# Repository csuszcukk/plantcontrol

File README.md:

# PlantControl
make a smart pot for plants

## Features

* Automatic watering and light control
* Humidity and temperature monitoring
* Soil temperature and moisture monitoring
* Low water level alert
* Custom water container design
* Compatible with all plants and pots

## How to Build It

1. **PCB Fabrication:** Order the PCBs from any manufacturer (ordering a stencil is recommended).
2. **Heat Dissipation (Optional):** If you plan to use LEDs, mount them on an aluminum sheet using thermal conductive tape for proper heat dissipation.
3. **Components:** Order the necessary components listed in the Bill of Materials (BOM) — feel free to modify or skip non-essential parts.
4. **3D Printing:** Print the structural parts (PLA is recommended for the main board enclosure, and PETG for the water container).
5. **Assembly:** Solder all components onto the PCB.
6. **Preparation:** Connect the boot configuration pins and plug in the power source.
7. **Flashing Interface:** Connect your USB-to-UART bridge (make sure RX and TX lines are swapped).
8. **Firmware Installation (MicroPython):** Flash the ESP32 with the MicroPython firmware (see the official [MicroPython ESP32 Documentation](https://docs.micropython.org/en/latest/esp32/tutorial/intro.html)).
9. **Uploading Code:** Flash `main.py` onto the board (follow this [MicroPython Flashing Guide](https://georgefreedom.com/ignition-sequence-how-to-flash-micropython-onto-your-esp32/)).
10. **Cleanup:** Remove the boot mode jumpers and the UART adapter, then disconnect power.
11. **Wiring:** Connect all peripherals and modules to their respective header pins (labels are silkscreened on the PCB for guidance).
12. **Final Mounting:** Secure the sensors and the main board inside the enclosure (double-sided mounting tape works great).
13. **Power On:** Reconnect power to the board.
14. **Done!** Your plant controller is ready to go.

> **Pro Tip:** On first boot (or if it cannot connect to a saved network), the device will host a Wi-Fi Access Point. Connect to it to enter your local Wi-Fi SSID and password via the captive portal. Don't forget to enter your ThingSpeak API key in the configuration file to enable telemetry logging!

## How It Works

PlantControl is an automated, ESP32-C6-powered plant monitoring and maintenance system running on custom MicroPython firmware. It continuously monitors environmental conditions and manages irrigation and lighting using asynchronous event loops.

### Core Architecture

* **Sensor Data Acquisition:** The system periodically samples soil moisture, ambient light, and air temperature/humidity levels. 
* **Automated Logic & Safety:** If soil moisture drops below the predefined threshold, the MCU triggers a relay/MOSFET to activate the water pump. It includes safety timers to prevent over-watering or running the pump dry.
* **Local UI & Status:** A circular GC9A01 SPI display provides real-time readout of plant metrics and device status directly on the enclosure.
* **Power & Load Management:** High-side MOSFET switching ensures power is delivered efficiently to peripherals (pumps, LEDs) only when needed, minimizing idle power consumption.
* **Connectivity & Telemetry:** Integrated Wi-Fi connects to local infrastructure to stream telemetry to ThingSpeak. If network connection fails, it automatically spins up a Wi-Fi Access Point with a captive portal for re-configuration.

## Component Sourcing & Logistics

To optimize the project budget and lead times, a hybrid sourcing strategy is used:

- **LCSC:** Used for standard SMD components, passives, ICs, and microcontrollers to take advantage of low bulk pricing.
- **HESTORE (EU Local Distributor):** Used for specific sensors, modules, and components unavailable on LCSC or needed quickly.

All BOM prices from HESTORE have been converted from HUF to USD using current market exchange rates.

## License

This project is licensed under the MIT License - see the [LICENSE](LICENSE) file for details.

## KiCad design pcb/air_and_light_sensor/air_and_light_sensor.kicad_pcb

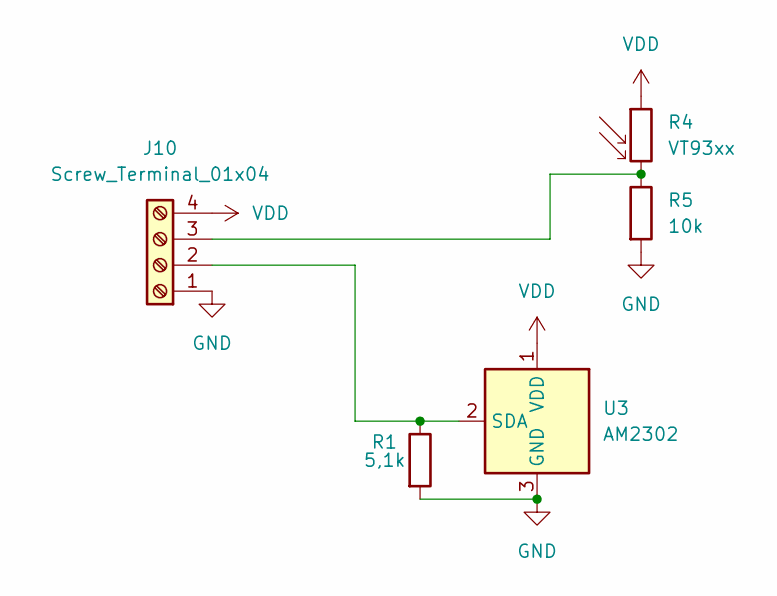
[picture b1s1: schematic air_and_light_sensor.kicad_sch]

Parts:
J10: Screw_Terminal_01x04; TerminalBlock_Phoenix_MKDS-1,5-4_1x04_P5.00mm_Horizontal; jlc part # C90087
R1: 5,1k; R_0603_1608Metric_Pad0.98x0.95mm_HandSolder
R4: VT93xx; R_LDR_4.9x4.2mm_P2.54mm_Vertical; jlc part # C10077
R5: 10k; R_0603_1608Metric_Pad0.98x0.95mm_HandSolder; jlc part # C2906982
U3: AM2302; ASAIR_AM2302_P2.54mm_Lead2.75mm_TabDown; jlc part # C83988

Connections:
GND: J10.1, R1.2, R5.2, U3.3 (GND), U3.4 (GND)
unnamed: J10.2, R1.1, U3.2 (SDA)
unnamed: J10.3, R4.2, R5.1
VDD: J10.4, R4.1, U3.1 (VDD)

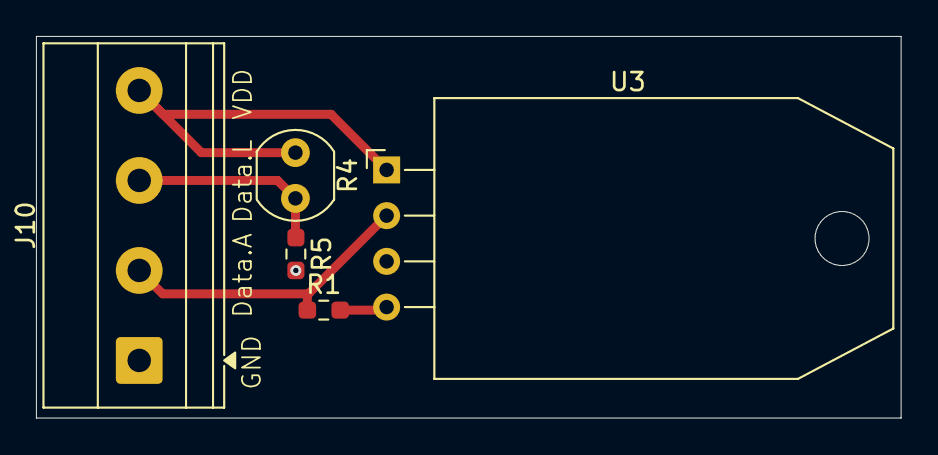
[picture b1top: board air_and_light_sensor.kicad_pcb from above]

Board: 2 copper layers, 48.0 x 21.2 mm, 5 parts (0 on the bottom side), 4 nets.

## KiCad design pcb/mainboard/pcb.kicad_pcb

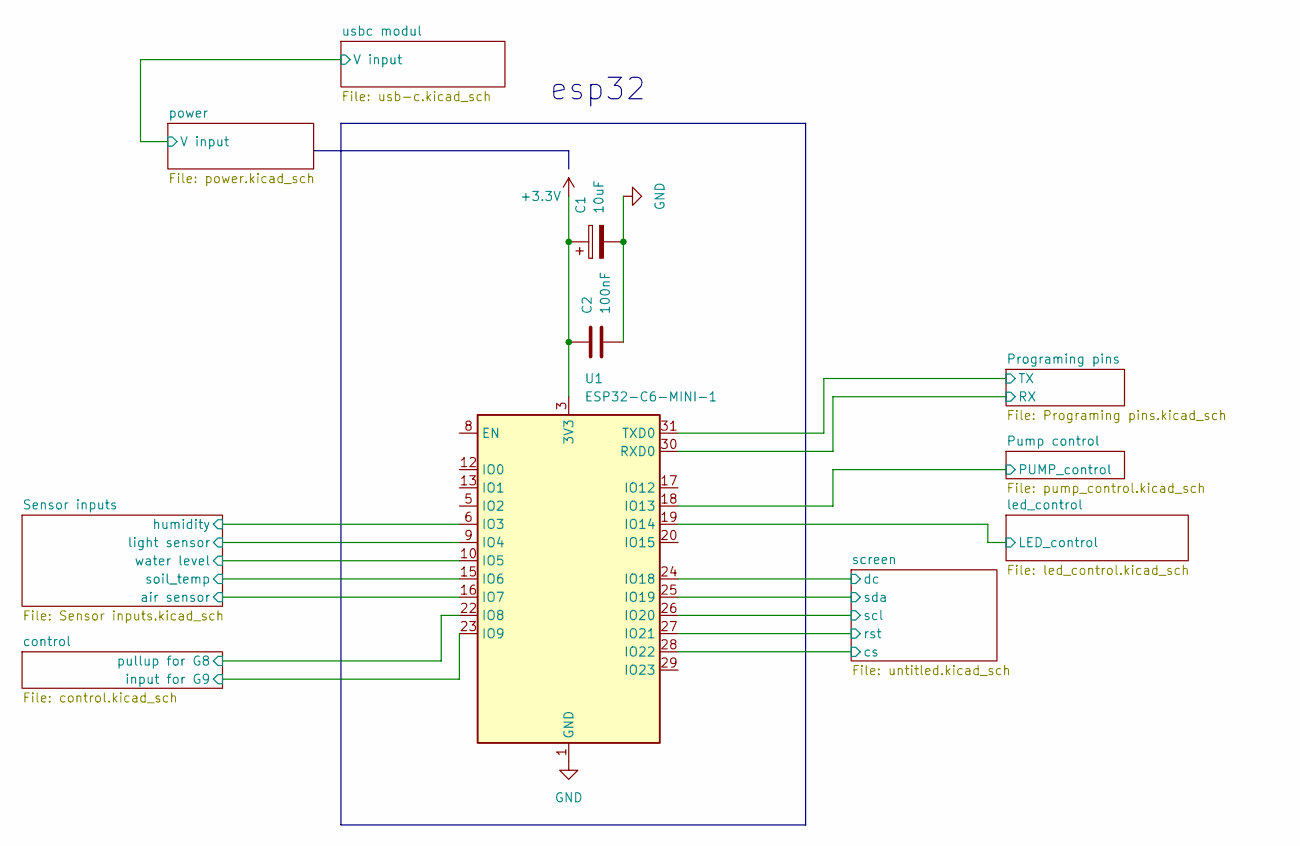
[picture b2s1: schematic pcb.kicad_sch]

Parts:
C1: 10uF; CP_Radial_D5.0mm_P2.00mm; jlc part # C216288
C2: 100nF; R_0603_1608Metric_Pad0.98x0.95mm_HandSolder; jlc part # C1591
U1: ESP32-C6-MINI-1; ESP32-C6-MINI-1psa; jlc part # C5736265

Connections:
+3.3V: C1.1, C2.1, U1.3 (3V3); also elsewhere on the board
/Programing pins/RX: U1.30 (RXD0); also elsewhere on the board
/Programing pins/TX: U1.31 (TXD0); also elsewhere on the board
/Pump control/PUMP_control: U1.18 (IO13); also elsewhere on the board
/Sensor inputs/air sensor: U1.16 (IO7); also elsewhere on the board
/Sensor inputs/humidity: U1.6 (IO3); also elsewhere on the board
/Sensor inputs/light sensor: U1.9 (IO4); also elsewhere on the board
/Sensor inputs/soil_temp: U1.15 (IO6); also elsewhere on the board
/Sensor inputs/water level: U1.10 (IO5); also elsewhere on the board
/control/input for G9: U1.23 (IO9); also elsewhere on the board
/control/pullup for G8: U1.22 (IO8); also elsewhere on the board
/led_control/LED_control: U1.19 (IO14); also elsewhere on the board
/screen/cs: U1.28 (IO22); also elsewhere on the board
/screen/dc: U1.24 (IO18); also elsewhere on the board
/screen/rst: U1.27 (IO21); also elsewhere on the board
/screen/scl: U1.26 (IO20); also elsewhere on the board
/screen/sda: U1.25 (IO19); also elsewhere on the board
GND: C1.2, C2.2, U1.1 (GND), U1.2 (GND), U1.11 (GND), U1.14 (GND), U1.36 (GND), U1.37 (GND), U1.38 (GND), U1.39 (GND), U1.40 (GND), U1.41 (GND), U1.42 (GND), U1.43 (GND), U1.44 (GND), U1.45 (GND), U1.46 (GND), U1.47 (GND), U1.48 (GND), U1.49 (GND), U1.50 (GND), U1.51 (GND), U1.52 (GND), U1.53 (GND); also elsewhere on the board

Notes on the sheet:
esp32

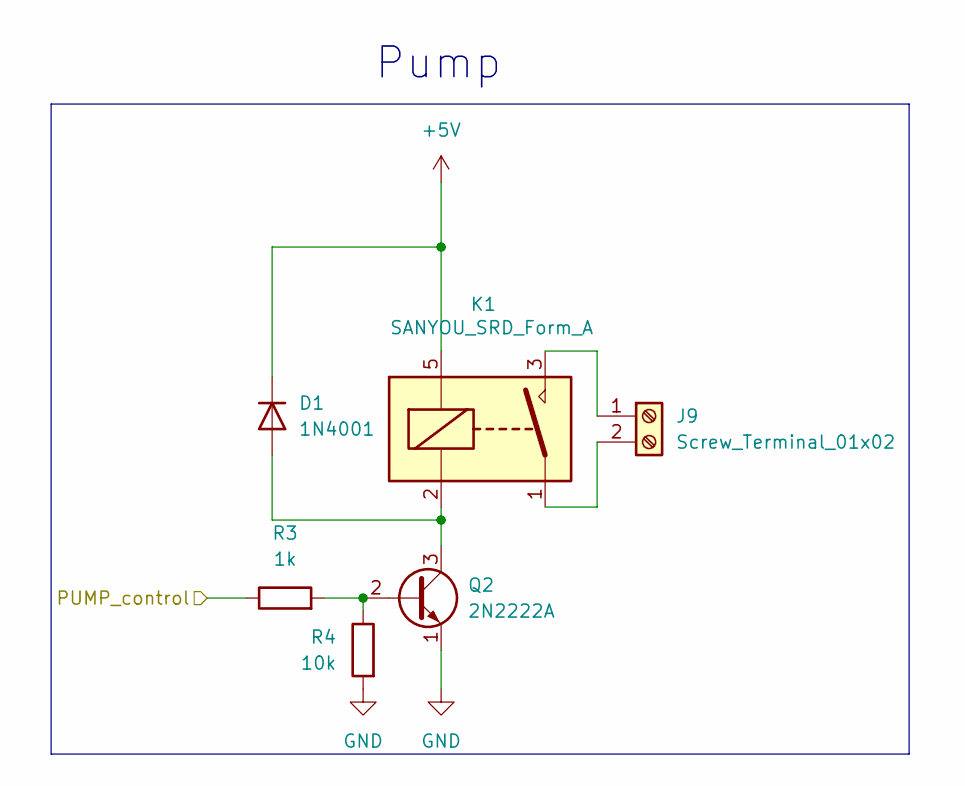
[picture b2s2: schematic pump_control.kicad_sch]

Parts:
D1: 1N4001; D_DO-41_SOD81_P10.16mm_Horizontal; jlc part # C2456
J9: Screw_Terminal_01x02; TerminalBlock_Phoenix_MKDS-1,5-2_1x02_P5.00mm_Horizontal; jlc part # C3703
K1: SANYOU_SRD_Form_A; Relay_SPDT_SANYOU_SRD_Series_Form_C; jlc part # C35449
Q2: 2N2222A; TO-39-3; jlc part # C118536
R3: 1k; R_0603_1608Metric_Pad0.98x0.95mm_HandSolder; jlc part # C2907002
R4: 10k; R_0603_1608Metric_Pad0.98x0.95mm_HandSolder

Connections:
+5V: D1.1 (K), K1.5; also elsewhere on the board
/Pump control/PUMP_control: R3.1; also elsewhere on the board
GND: Q2.1 (E), R4.2; also elsewhere on the board
unnamed: D1.2 (A), K1.2, Q2.3 (C)
unnamed: J9.1, K1.3
unnamed: J9.2, K1.1
unnamed: Q2.2 (B), R3.2, R4.1

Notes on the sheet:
Pump

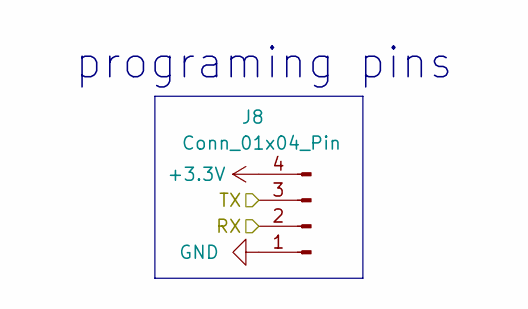
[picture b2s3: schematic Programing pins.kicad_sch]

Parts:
J8: Conn_01x04_Pin; PinSocket_1x04_P2.54mm_Vertical; jlc part # C37208

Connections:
+3.3V: J8.4; also elsewhere on the board
/Programing pins/RX: J8.2; also elsewhere on the board
/Programing pins/TX: J8.3; also elsewhere on the board
GND: J8.1; also elsewhere on the board

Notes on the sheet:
programing pins

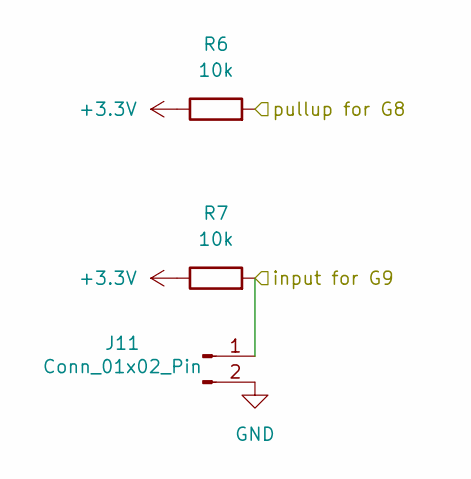
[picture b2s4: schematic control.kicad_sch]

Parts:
J11: Conn_01x02_Pin; PinHeader_1x02_P2.54mm_Vertical; jlc part # C37208
R6, R7: 10k; R_0603_1608Metric_Pad0.98x0.95mm_HandSolder; jlc part # C2906982

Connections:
+3.3V: R6.1, R7.1; also elsewhere on the board
/control/input for G9: J11.1, R7.2; also elsewhere on the board
/control/pullup for G8: R6.2; also elsewhere on the board
GND: J11.2; also elsewhere on the board

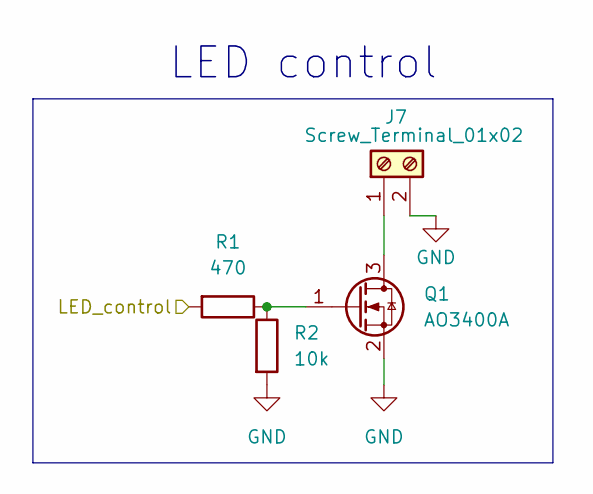
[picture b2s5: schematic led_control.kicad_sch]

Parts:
J7: Screw_Terminal_01x02; TerminalBlock_Phoenix_MKDS-1,5-2_1x02_P5.00mm_Horizontal; jlc part # C3703
Q1: AO3400A; SOT-23; jlc part # C20917
R1: 470; R_0603_1608Metric_Pad0.98x0.95mm_HandSolder; jlc part # C23179
R2: 10k; R_0603_1608Metric_Pad0.98x0.95mm_HandSolder; jlc part # C2906982

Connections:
/led_control/LED_control: R1.2; also elsewhere on the board
GND: J7.2, Q1.2 (S), R2.2; also elsewhere on the board
unnamed: J7.1, Q1.3 (D)
unnamed: Q1.1 (G), R1.1, R2.1

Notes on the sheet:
LED control

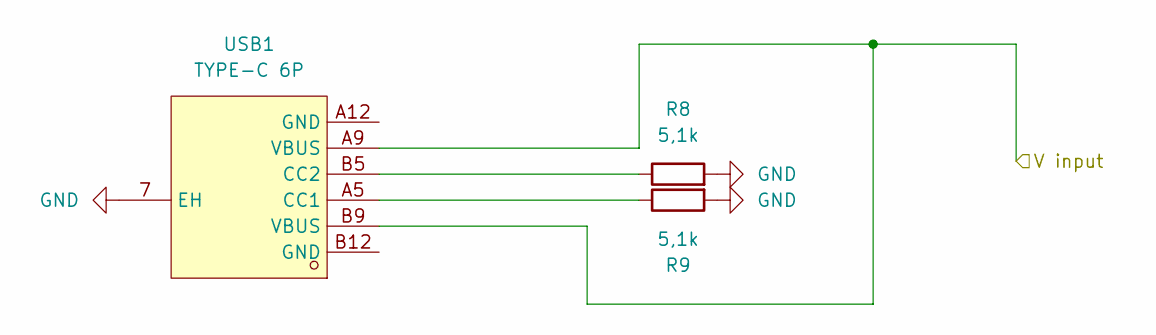
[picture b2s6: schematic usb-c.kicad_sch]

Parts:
R8, R9: 5,1k; R_0603_1608Metric_Pad0.98x0.95mm_HandSolder; jlc part # C177348
USB1: TYPE-C 6P; TYPE-C-SMD_TYPE-C-6P-073; MPN TYPE-C 6P(073); jlc part # C668623

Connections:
+5V: USB1.A9 (VBUS), USB1.B9 (VBUS); also elsewhere on the board
GND: R8.2, R9.2, USB1.7 (EH); also elsewhere on the board
unnamed: R9.1, USB1.A5 (CC1)
unnamed: R8.1, USB1.B5 (CC2)

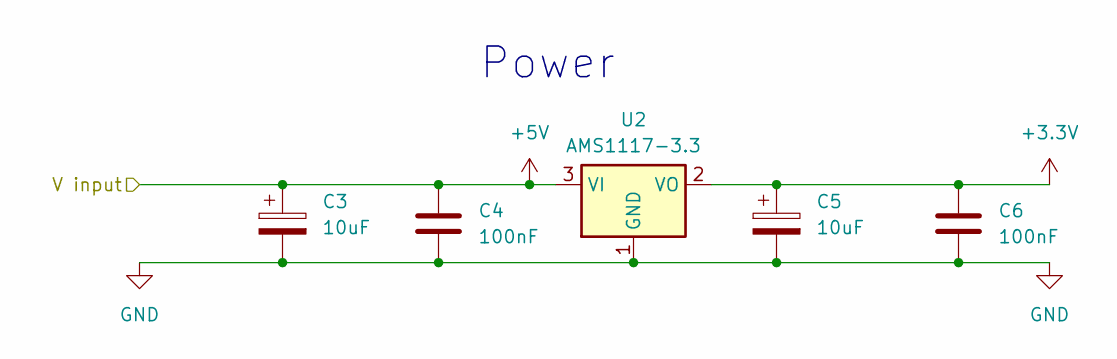
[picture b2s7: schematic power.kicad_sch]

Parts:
C3, C5: 10uF; CP_Radial_D5.0mm_P2.00mm; jlc part # C216288
C4, C6: 100nF; R_0603_1608Metric_Pad0.98x0.95mm_HandSolder; jlc part # C1591
U2: AMS1117-3.3; SOT-223-3_TabPin2; jlc part # C6186

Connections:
+3.3V: C5.1, C6.1, U2.2 (VO); also elsewhere on the board
+5V: C3.1, C4.1, U2.3 (VI); also elsewhere on the board
GND: C3.2, C4.2, C5.2, C6.2, U2.1 (GND); also elsewhere on the board

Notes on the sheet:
Power

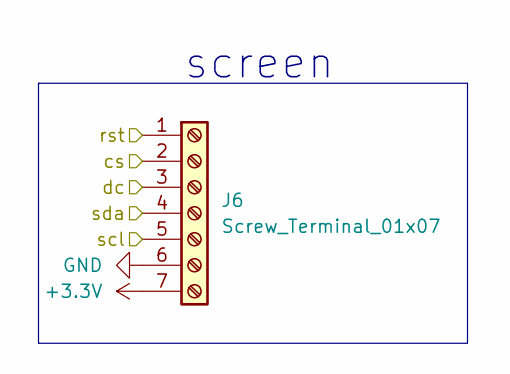
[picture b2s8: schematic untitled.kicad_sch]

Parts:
J6: Screw_Terminal_01x07; TerminalBlock_Phoenix_MKDS-1,5-7_1x07_P5.00mm_Horizontal; jlc part # C395855

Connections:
+3.3V: J6.7; also elsewhere on the board
/screen/cs: J6.2; also elsewhere on the board
/screen/dc: J6.3; also elsewhere on the board
/screen/rst: J6.1; also elsewhere on the board
/screen/scl: J6.5; also elsewhere on the board
/screen/sda: J6.4; also elsewhere on the board
GND: J6.6; also elsewhere on the board

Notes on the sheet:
screen

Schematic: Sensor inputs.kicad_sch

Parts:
J2: Screw_Terminal_01x04; TerminalBlock_Phoenix_MKDS-1,5-4_1x04_P5.00mm_Horizontal; jlc part # C90087
J3: Screw_Terminal_01x02; TerminalBlock_Phoenix_MKDS-1,5-2_1x02_P5.00mm_Horizontal; jlc part # C3703
J4, J5: Screw_Terminal_01x03; TerminalBlock_Phoenix_MKDS-1,5-3_1x03_P5.00mm_Horizontal; jlc part # C8270

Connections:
+3.3V: J2.4, J4.3, J5.3; also elsewhere on the board
/Sensor inputs/air sensor: J2.2; also elsewhere on the board
/Sensor inputs/humidity: J5.2; also elsewhere on the board
/Sensor inputs/light sensor: J2.3; also elsewhere on the board
/Sensor inputs/soil_temp: J4.2; also elsewhere on the board
/Sensor inputs/water level: J3.1; also elsewhere on the board
GND: J2.1, J3.2, J4.1, J5.1; also elsewhere on the board

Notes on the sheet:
water level sensor
soil tempature input
light and air sensor input
soil humuidity input

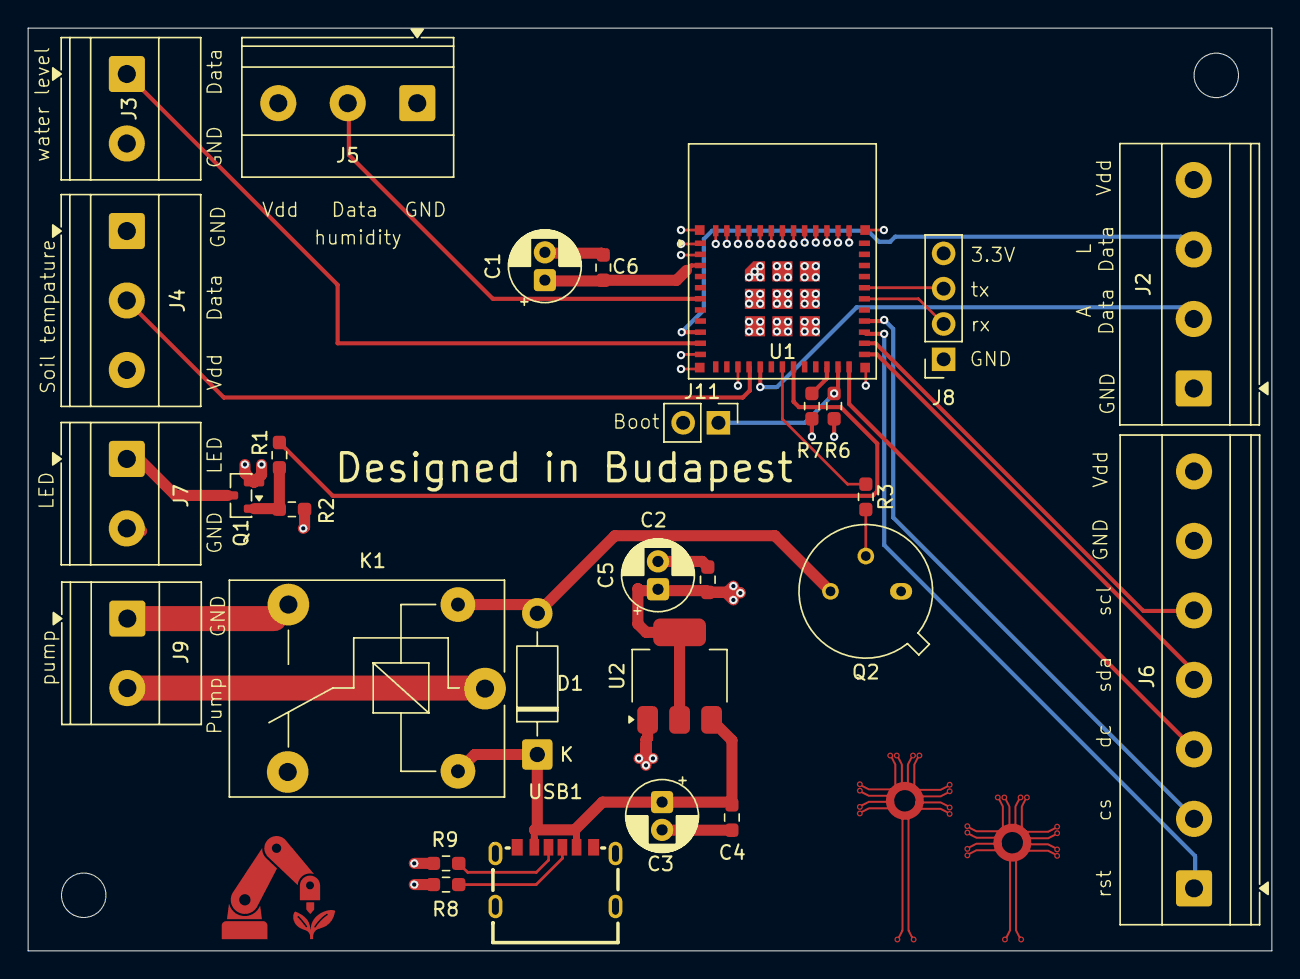
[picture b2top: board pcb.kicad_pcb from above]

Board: 4 copper layers, 89.5 x 66.4 mm, 29 parts (0 on the bottom side), 27 nets.
